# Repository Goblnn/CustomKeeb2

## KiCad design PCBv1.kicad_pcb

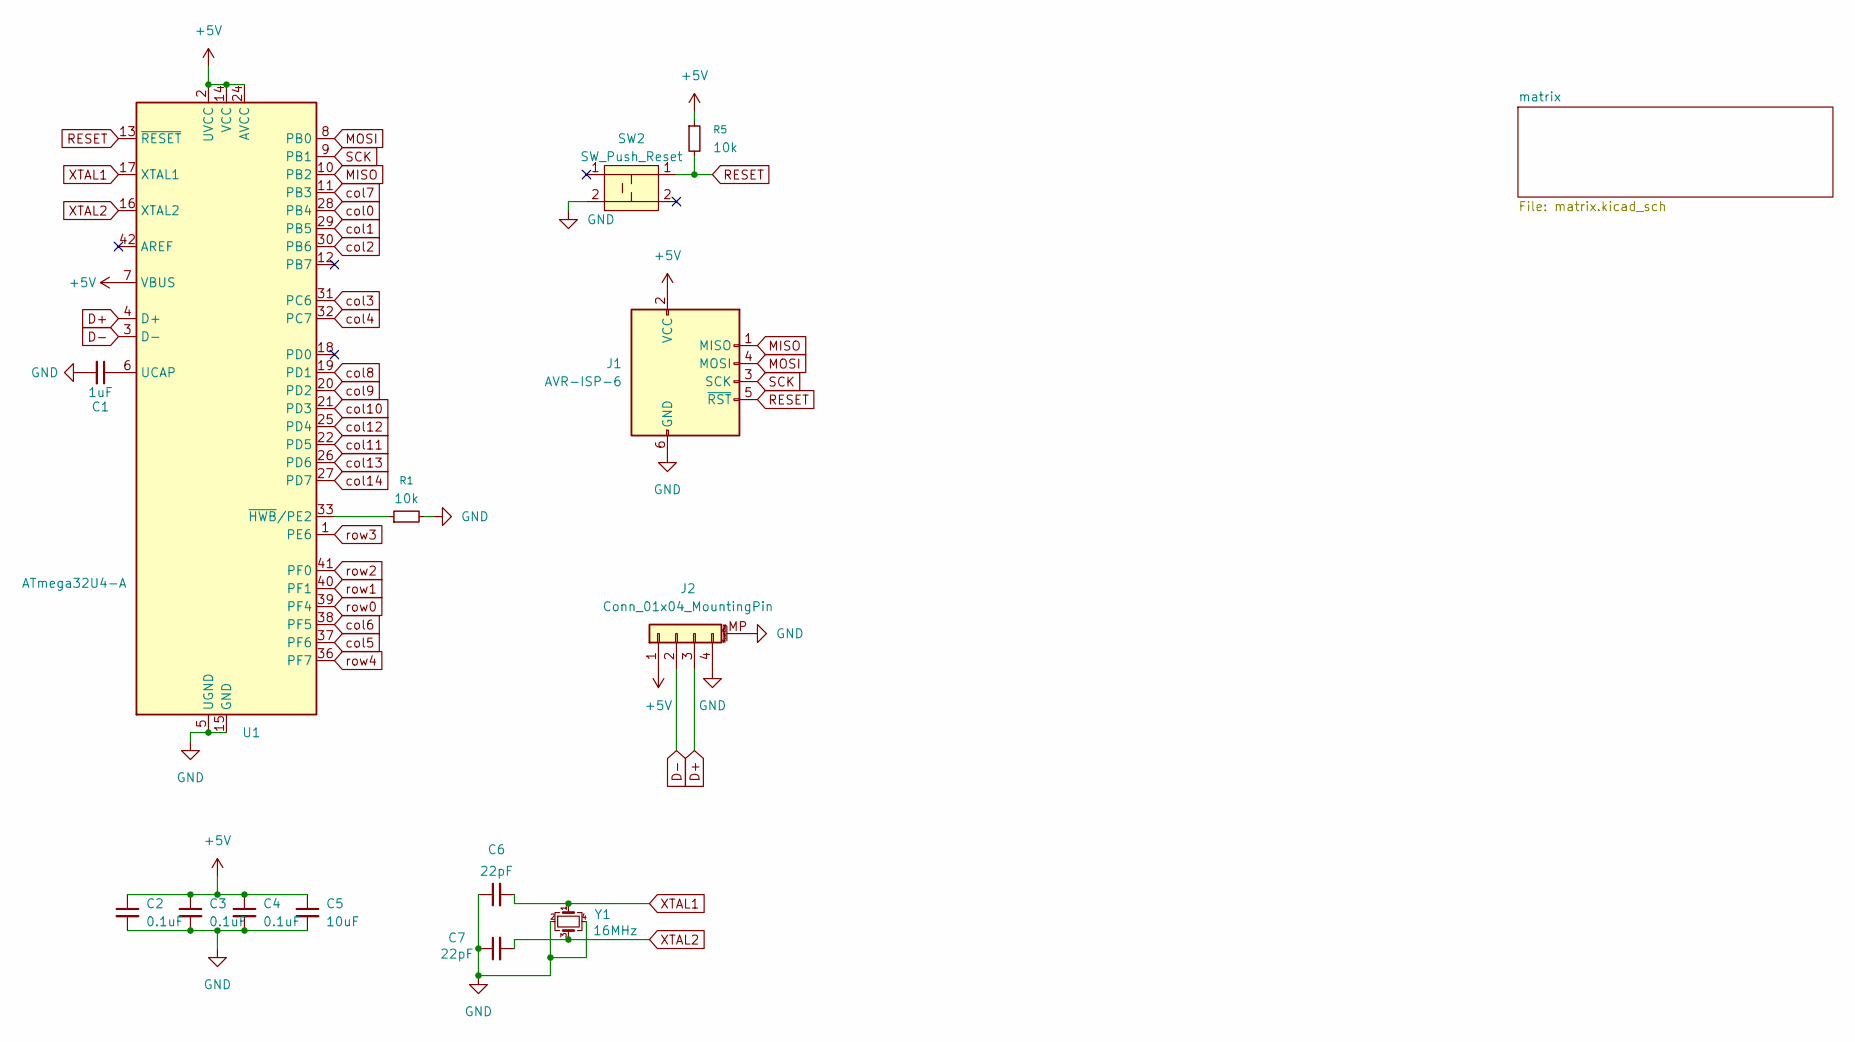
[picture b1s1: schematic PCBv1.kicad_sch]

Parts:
C1: 1uF; C_0805_2012Metric_Pad1.18x1.45mm_HandSolder
C2, C3, C4: 0.1uF; C_0805_2012Metric_Pad1.18x1.45mm_HandSolder
C5: 10uF; C_0805_2012Metric_Pad1.18x1.45mm_HandSolder
C6, C7: 22pF; C_0805_2012Metric_Pad1.18x1.45mm_HandSolder
J1: AVR-ISP-6; Reset_Pretty-Mask
J2: Conn_01x04_MountingPin; JST_SH_SM04B-SRSS-TB_1x04-1MP_P1.00mm_Horizontal
R1, R5: 10k; R_0805_2012Metric_Pad1.20x1.40mm_HandSolder
SW2: SW_Push_Reset; SW_SPST_SKQG_WithStem
U1: ATmega32U4-A; TQFP-44_10x10mm_P0.8mm
Y1: 16MHz; Crystal_SMD_3225-4Pin_3.2x2.5mm_HandSoldering

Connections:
+5V: C2.1, C3.1, C4.1, C5.1, J1.2 (VCC), J2.1, R5.1, U1.2 (UVCC), U1.7 (VBUS), U1.14 (VCC), U1.24 (AVCC), U1.34 (VCC), U1.44 (AVCC)
D+: J2.3, U1.4 (D+)
D-: J2.2, U1.3 (D-)
GND: C1.2, C2.2, C3.2, C4.2, C5.2, C6.1, C7.1, J1.6 (GND), J2.4, J2.MP (MountPin), R1.2, SW2.2, U1.5 (UGND), U1.15 (GND), U1.23 (GND), U1.35 (GND), U1.43 (GND), Y1.2, Y1.4
MISO: J1.1 (MISO), U1.10 (PB2)
MOSI: J1.4 (MOSI), U1.8 (PB0)
unnamed: C1.1, U1.6 (UCAP)
unnamed: R1.1, U1.33 (~HWB/PE2)
RESET: J1.5 (~RST), R5.2, SW2.1, U1.13 (~RESET)
SCK: J1.3 (SCK), U1.9 (PB1)
XTAL1: C6.2, U1.17 (XTAL1), Y1.1
XTAL2: C7.2, U1.16 (XTAL2), Y1.3
col0: U1.28 (PB4); also elsewhere on the board
col1: U1.29 (PB5); also elsewhere on the board
col2: U1.30 (PB6); also elsewhere on the board
col3: U1.31 (PC6); also elsewhere on the board
col4: U1.32 (PC7); also elsewhere on the board
col5: U1.37 (PF6); also elsewhere on the board
col6: U1.38 (PF5); also elsewhere on the board
col7: U1.11 (PB3); also elsewhere on the board
col8: U1.19 (PD1); also elsewhere on the board
col9: U1.20 (PD2); also elsewhere on the board
col10: U1.21 (PD3); also elsewhere on the board
col11: U1.22 (PD5); also elsewhere on the board
col12: U1.25 (PD4); also elsewhere on the board
col13: U1.26 (PD6); also elsewhere on the board
col14: U1.27 (PD7); also elsewhere on the board
row0: U1.39 (PF4); also elsewhere on the board
row1: U1.40 (PF1); also elsewhere on the board
row2: U1.41 (PF0); also elsewhere on the board
row3: U1.1 (PE6); also elsewhere on the board
row4: U1.36 (PF7); also elsewhere on the board

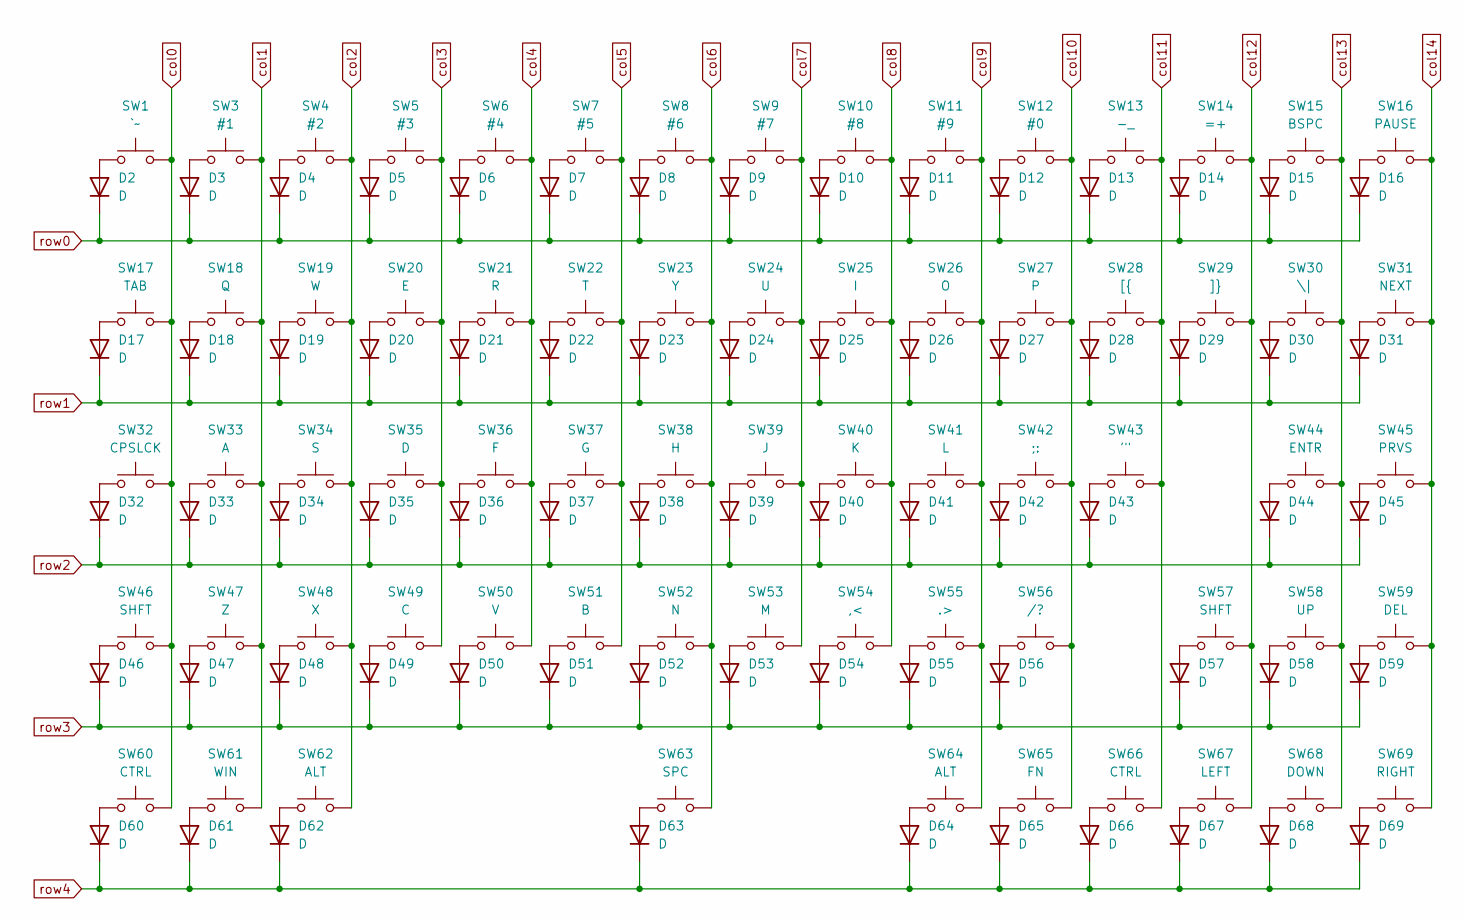
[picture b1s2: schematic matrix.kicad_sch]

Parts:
D2, D3, D4, D5, D6, D7, D8, D9, D10, D11, D12, D13, D14, D15, D16, D17, D18, D19, D20, D21, D22, D23, D24, D25, D26, D27, D28, D29, D30, D31, D32, D33, D34, D35, D36, D37, D38, D39, D40, D41, D42, D43, D44, D45, D46, D47, D48, D49, D50, D51, D52, D53, D54, D55, D56, D57, D58, D59, D60, D61, D62, D63, D64, D65, D66, D67, D68, D69: D; D_SOD-123
SW1: `~; MXOnly-1U-NoLED
SW3: #1; MXOnly-1U-NoLED
SW4: #2; MXOnly-1U-NoLED
SW5: #3; MXOnly-1U-NoLED
SW6: #4; MXOnly-1U-NoLED
SW7: #5; MXOnly-1U-NoLED
SW8: #6; MXOnly-1U-NoLED
SW9: #7; MXOnly-1U-NoLED
SW10: #8; MXOnly-1U-NoLED
SW11: #9; MXOnly-1U-NoLED
SW12: #0; MXOnly-1U-NoLED
SW13: -_; MXOnly-1U-NoLED
SW14: =+; MXOnly-1U-NoLED
SW15: BSPC; MXOnly-2U-NoLED
SW16: PAUSE; MXOnly-1U-NoLED
SW17: TAB; MXOnly-1.5U-NoLED
SW18: Q; MXOnly-1U-NoLED
SW19: W; MXOnly-1U-NoLED
SW20: E; MXOnly-1U-NoLED
SW21: R; MXOnly-1U-NoLED
SW22: T; MXOnly-1U-NoLED
SW23: Y; MXOnly-1U-NoLED
SW24: U; MXOnly-1U-NoLED
SW25: I; MXOnly-1U-NoLED
SW26: O; MXOnly-1U-NoLED
SW27: P; MXOnly-1U-NoLED
SW28: [{; MXOnly-1U-NoLED
SW29: ]}; MXOnly-1U-NoLED
SW30: \|; MXOnly-1.5U-NoLED
SW31: NEXT; MXOnly-1U-NoLED
SW32: CPSLCK; MXOnly-1.75U-NoLED
SW33: A; MXOnly-1U-NoLED
SW34: S; MXOnly-1U-NoLED
SW35: D; MXOnly-1U-NoLED
SW36: F; MXOnly-1U-NoLED
SW37: G; MXOnly-1U-NoLED
SW38: H; MXOnly-1U-NoLED
SW39: J; MXOnly-1U-NoLED
SW40: K; MXOnly-1U-NoLED
SW41: L; MXOnly-1U-NoLED
SW42: ;:; MXOnly-1U-NoLED
SW43: '"; MXOnly-1U-NoLED
SW44: ENTR; MXOnly-2.25U-NoLED
SW45: PRVS; MXOnly-1U-NoLED
SW46: SHFT; MXOnly-2.25U-NoLED
SW47: Z; MXOnly-1U-NoLED
SW48: X; MXOnly-1U-NoLED
SW49: C; MXOnly-1U-NoLED
SW50: V; MXOnly-1U-NoLED
SW51: B; MXOnly-1U-NoLED
SW52: N; MXOnly-1U-NoLED
SW53: M; MXOnly-1U-NoLED
SW54: ,<; MXOnly-1U-NoLED
SW55: .>; MXOnly-1U-NoLED
SW56: /?; MXOnly-1U-NoLED
SW57: SHFT; MXOnly-1.75U-NoLED
SW58: UP; MXOnly-1U-NoLED
SW59: DEL; MXOnly-1U-NoLED
SW60: CTRL; MXOnly-1.25U-NoLED
SW61: WIN; MXOnly-1.25U-NoLED
SW62: ALT; MXOnly-1.25U-NoLED
SW63: SPC; MXOnly-6.25U-NoLED
SW64: ALT; MXOnly-1U-NoLED
SW65: FN; MXOnly-1U-NoLED
SW66: CTRL; MXOnly-1U-NoLED
SW67: LEFT; MXOnly-1U-NoLED
SW68: DOWN; MXOnly-1U-NoLED
SW69: RIGHT; MXOnly-1U-NoLED

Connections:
unnamed: D2.2 (A), SW1.1
unnamed: D3.2 (A), SW3.1
unnamed: D4.2 (A), SW4.1
unnamed: D5.2 (A), SW5.1
unnamed: D6.2 (A), SW6.1
unnamed: D7.2 (A), SW7.1
unnamed: D8.2 (A), SW8.1
unnamed: D9.2 (A), SW9.1
unnamed: D10.2 (A), SW10.1
unnamed: D11.2 (A), SW11.1
unnamed: D12.2 (A), SW12.1
unnamed: D13.2 (A), SW13.1
unnamed: D14.2 (A), SW14.1
unnamed: D15.2 (A), SW15.1
unnamed: D16.2 (A), SW16.1
unnamed: D17.2 (A), SW17.1
unnamed: D18.2 (A), SW18.1
unnamed: D19.2 (A), SW19.1
unnamed: D20.2 (A), SW20.1
unnamed: D21.2 (A), SW21.1
unnamed: D22.2 (A), SW22.1
unnamed: D23.2 (A), SW23.1
unnamed: D24.2 (A), SW24.1
unnamed: D25.2 (A), SW25.1
unnamed: D26.2 (A), SW26.1
unnamed: D27.2 (A), SW27.1
unnamed: D28.2 (A), SW28.1
unnamed: D29.2 (A), SW29.1
unnamed: D30.2 (A), SW30.1
unnamed: D31.2 (A), SW31.1
unnamed: D32.2 (A), SW32.1
unnamed: D33.2 (A), SW33.1
unnamed: D34.2 (A), SW34.1
unnamed: D35.2 (A), SW35.1
unnamed: D36.2 (A), SW36.1
unnamed: D37.2 (A), SW37.1
unnamed: D38.2 (A), SW38.1
unnamed: D39.2 (A), SW39.1
unnamed: D40.2 (A), SW40.1
unnamed: D41.2 (A), SW41.1
unnamed: D42.2 (A), SW42.1
unnamed: D43.2 (A), SW43.1
unnamed: D44.2 (A), SW44.1
unnamed: D45.2 (A), SW45.1
unnamed: D46.2 (A), SW46.1
unnamed: D47.2 (A), SW47.1
unnamed: D48.2 (A), SW48.1
unnamed: D49.2 (A), SW49.1
unnamed: D50.2 (A), SW50.1
unnamed: D51.2 (A), SW51.1
unnamed: D52.2 (A), SW52.1
unnamed: D53.2 (A), SW53.1
unnamed: D54.2 (A), SW54.1
unnamed: D55.2 (A), SW55.1
unnamed: D56.2 (A), SW56.1
unnamed: D57.2 (A), SW57.1
unnamed: D58.2 (A), SW58.1
unnamed: D59.2 (A), SW59.1
unnamed: D60.2 (A), SW60.1
unnamed: D61.2 (A), SW61.1
unnamed: D62.2 (A), SW62.1
unnamed: D63.2 (A), SW63.1
unnamed: D64.2 (A), SW64.1
unnamed: D65.2 (A), SW65.1
unnamed: D66.2 (A), SW66.1
unnamed: D67.2 (A), SW67.1
unnamed: D68.2 (A), SW68.1
unnamed: D69.2 (A), SW69.1
col0: SW1.2, SW17.2, SW32.2, SW46.2, SW60.2; also elsewhere on the board
col1: SW3.2, SW18.2, SW33.2, SW47.2, SW61.2; also elsewhere on the board
col2: SW4.2, SW19.2, SW34.2, SW48.2, SW62.2; also elsewhere on the board
col3: SW5.2, SW20.2, SW35.2, SW49.2; also elsewhere on the board
col4: SW6.2, SW21.2, SW36.2, SW50.2; also elsewhere on the board
col5: SW7.2, SW22.2, SW37.2, SW51.2; also elsewhere on the board
col6: SW8.2, SW23.2, SW38.2, SW52.2, SW63.2; also elsewhere on the board
col7: SW9.2, SW24.2, SW39.2, SW53.2; also elsewhere on the board
col8: SW10.2, SW25.2, SW40.2, SW54.2; also elsewhere on the board
col9: SW11.2, SW26.2, SW41.2, SW55.2, SW64.2; also elsewhere on the board
col10: SW12.2, SW27.2, SW42.2, SW56.2, SW65.2; also elsewhere on the board
col11: SW13.2, SW28.2, SW43.2, SW66.2; also elsewhere on the board
col12: SW14.2, SW29.2, SW57.2, SW67.2; also elsewhere on the board
col13: SW15.2, SW30.2, SW44.2, SW58.2, SW68.2; also elsewhere on the board
col14: SW16.2, SW31.2, SW45.2, SW59.2, SW69.2; also elsewhere on the board
row0: D2.1 (K), D3.1 (K), D4.1 (K), D5.1 (K), D6.1 (K), D7.1 (K), D8.1 (K), D9.1 (K), D10.1 (K), D11.1 (K), D12.1 (K), D13.1 (K), D14.1 (K), D15.1 (K), D16.1 (K); also elsewhere on the board
row1: D17.1 (K), D18.1 (K), D19.1 (K), D20.1 (K), D21.1 (K), D22.1 (K), D23.1 (K), D24.1 (K), D25.1 (K), D26.1 (K), D27.1 (K), D28.1 (K), D29.1 (K), D30.1 (K), D31.1 (K); also elsewhere on the board
row2: D32.1 (K), D33.1 (K), D34.1 (K), D35.1 (K), D36.1 (K), D37.1 (K), D38.1 (K), D39.1 (K), D40.1 (K), D41.1 (K), D42.1 (K), D43.1 (K), D44.1 (K), D45.1 (K); also elsewhere on the board
row3: D46.1 (K), D47.1 (K), D48.1 (K), D49.1 (K), D50.1 (K), D51.1 (K), D52.1 (K), D53.1 (K), D54.1 (K), D55.1 (K), D56.1 (K), D57.1 (K), D58.1 (K), D59.1 (K); also elsewhere on the board
row4: D60.1 (K), D61.1 (K), D62.1 (K), D63.1 (K), D64.1 (K), D65.1 (K), D66.1 (K), D67.1 (K), D68.1 (K), D69.1 (K); also elsewhere on the board

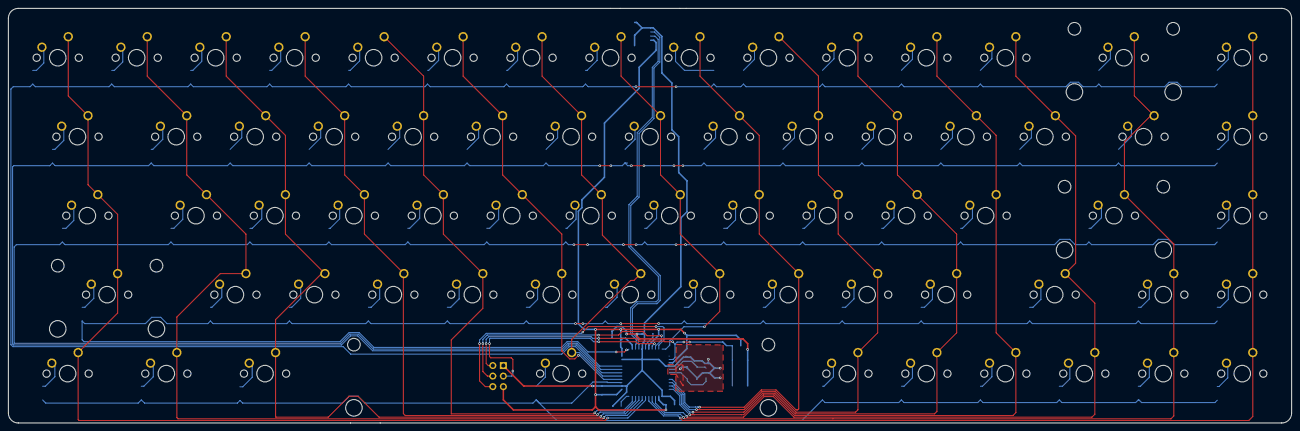
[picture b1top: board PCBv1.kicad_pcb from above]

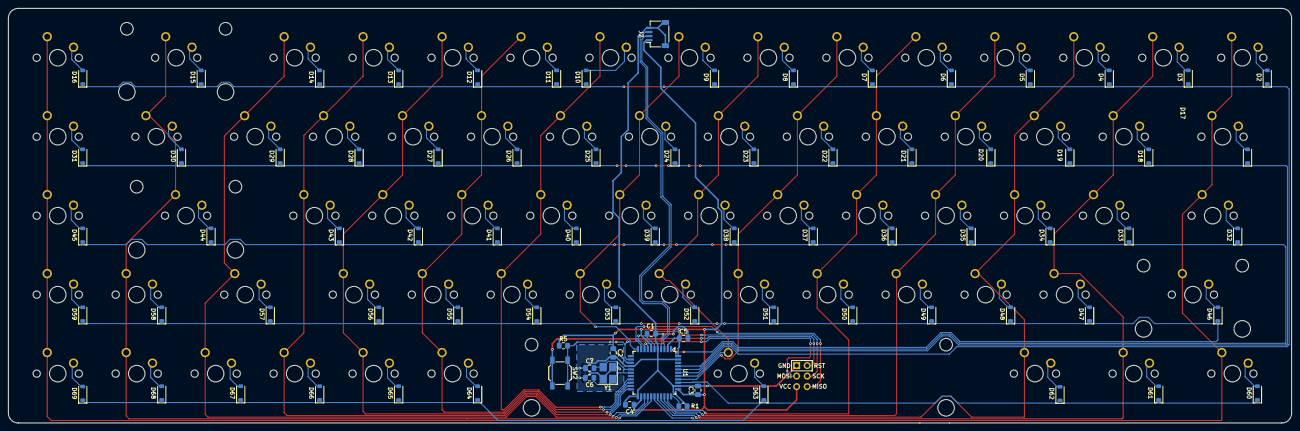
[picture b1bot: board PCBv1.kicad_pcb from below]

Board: 2 copper layers, 309.6 x 100.0 mm, 150 parts (82 on the bottom side), 100 nets.

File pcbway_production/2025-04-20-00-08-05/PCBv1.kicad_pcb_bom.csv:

Designator,Quantity,Value,Footprint,Package,MPN,DNP,Mount_Type,Description,Sim.Device,Sim.Pins
C1,1,1uF,C_0805_2012Metric_Pad1.18x1.45mm_HandSolder,,,,smt,"Unpolarized capacitor, small symbol",,
"C2, C3, C4",3,0.1uF,C_0805_2012Metric_Pad1.18x1.45mm_HandSolder,,,,smt,"Unpolarized capacitor, small symbol",,
C5,1,10uF,C_0805_2012Metric_Pad1.18x1.45mm_HandSolder,,,,smt,"Unpolarized capacitor, small symbol",,
"C6, C7",2,22pF,C_0805_2012Metric_Pad1.18x1.45mm_HandSolder,,,,smt,"Unpolarized capacitor, small symbol",,
D1,1,PRTR5V0U2X,SOT-143,,,,smt,"Ultra low capacitance double rail-to-rail ESD protection diode, SOT-143",,
"D10, D11, D12, D13, D14, D15, D16, D17, D18, D19, D2, D20, D21, D22, D23, D24, D25, D26, D27, D28, D29, D3, D30, D31, D32, D33, D34, D35, D36, D37, D38, D39, D4, D40, D41, D42, D43, D44, D45, D46, D47, D48, D49, D5, D50, D51, D52, D53, D54, D55, D56, D57, D58, D59, D6, D60, D61, D62, D63, D64, D65, D66, D67, D68, D69, D7, D8, D9",68,D,D_SOD-123,,,,smt,Diode,D,1=K 2=A
F1,1,500m,Fuse_1206_3216Metric_Pad1.42x1.75mm_HandSolder,,,,smt,"Resettable fuse, polymeric positive temperature coefficient, small symbol",,
J1,1,AVR-ISP-6,Reset_Pretty-Mask,,,,tht,Atmel 6-pin ISP connector,,
"R1, R5",2,10k,R_0805_2012Metric_Pad1.20x1.40mm_HandSolder,,,,smt,"Resistor, small symbol",,
"R6, R7",2,22,R_0805_2012Metric_Pad1.20x1.40mm_HandSolder,,,,smt,"Resistor, small symbol",,
"R8, R9",2,5.1k,R_0805_2012Metric_Pad1.20x1.40mm_HandSolder,,,,smt,"Resistor, small symbol",,
SW1,1,`~,MXOnly-1U-NoLED,,,,tht,"Push button switch, generic, two pins",,
SW10,1,#8,MXOnly-1U-NoLED,,,,tht,"Push button switch, generic, two pins",,
SW11,1,#9,MXOnly-1U-NoLED,,,,tht,"Push button switch, generic, two pins",,
SW12,1,#0,MXOnly-1U-NoLED,,,,tht,"Push button switch, generic, two pins",,
SW13,1,-_,MXOnly-1U-NoLED,,,,tht,"Push button switch, generic, two pins",,
SW14,1,=+,MXOnly-1U-NoLED,,,,tht,"Push button switch, generic, two pins",,
SW15,1,BSPC,MXOnly-2U-NoLED,,,,tht,"Push button switch, generic, two pins",,
SW16,1,PAUSE,MXOnly-1U-NoLED,,,,tht,"Push button switch, generic, two pins",,
SW17,1,TAB,MXOnly-1.5U-NoLED,,,,tht,"Push button switch, generic, two pins",,
SW18,1,Q,MXOnly-1U-NoLED,,,,tht,"Push button switch, generic, two pins",,
SW19,1,W,MXOnly-1U-NoLED,,,,tht,"Push button switch, generic, two pins",,
SW2,1,SW_Push_Reset,SW_SPST_SKQG_WithStem,,,,smt,,,
SW20,1,E,MXOnly-1U-NoLED,,,,tht,"Push button switch, generic, two pins",,
SW21,1,R,MXOnly-1U-NoLED,,,,tht,"Push button switch, generic, two pins",,
SW22,1,T,MXOnly-1U-NoLED,,,,tht,"Push button switch, generic, two pins",,
SW23,1,Y,MXOnly-1U-NoLED,,,,tht,"Push button switch, generic, two pins",,
SW24,1,U,MXOnly-1U-NoLED,,,,tht,"Push button switch, generic, two pins",,
SW25,1,I,MXOnly-1U-NoLED,,,,tht,"Push button switch, generic, two pins",,
SW26,1,O,MXOnly-1U-NoLED,,,,tht,"Push button switch, generic, two pins",,
SW27,1,P,MXOnly-1U-NoLED,,,,tht,"Push button switch, generic, two pins",,
SW28,1,[{,MXOnly-1U-NoLED,,,,tht,"Push button switch, generic, two pins",,
SW29,1,]},MXOnly-1U-NoLED,,,,tht,"Push button switch, generic, two pins",,
SW3,1,#1,MXOnly-1U-NoLED,,,,tht,"Push button switch, generic, two pins",,
SW30,1,\|,MXOnly-1.5U-NoLED,,,,tht,"Push button switch, generic, two pins",,
SW31,1,NEXT,MXOnly-1U-NoLED,,,,tht,"Push button switch, generic, two pins",,
SW32,1,CPSLCK,MXOnly-1.75U-NoLED,,,,tht,"Push button switch, generic, two pins",,
SW33,1,A,MXOnly-1U-NoLED,,,,tht,"Push button switch, generic, two pins",,
SW34,1,S,MXOnly-1U-NoLED,,,,tht,"Push button switch, generic, two pins",,
SW35,1,D,MXOnly-1U-NoLED,,,,tht,"Push button switch, generic, two pins",,
SW36,1,F,MXOnly-1U-NoLED,,,,tht,"Push button switch, generic, two pins",,
SW37,1,G,MXOnly-1U-NoLED,,,,tht,"Push button switch, generic, two pins",,
SW38,1,H,MXOnly-1U-NoLED,,,,tht,"Push button switch, generic, two pins",,
SW39,1,J,MXOnly-1U-NoLED,,,,tht,"Push button switch, generic, two pins",,
SW4,1,#2,MXOnly-1U-NoLED,,,,tht,"Push button switch, generic, two pins",,
SW40,1,K,MXOnly-1U-NoLED,,,,tht,"Push button switch, generic, two pins",,
SW41,1,L,MXOnly-1U-NoLED,,,,tht,"Push button switch, generic, two pins",,
SW42,1,;:,MXOnly-1U-NoLED,,,,tht,"Push button switch, generic, two pins",,
SW43,1,"'""",MXOnly-1U-NoLED,,,,tht,"Push button switch, generic, two pins",,
SW44,1,ENTR,MXOnly-2.25U-NoLED,,,,tht,"Push button switch, generic, two pins",,
SW45,1,PRVS,MXOnly-1U-NoLED,,,,tht,"Push button switch, generic, two pins",,
SW46,1,SHFT,MXOnly-2.25U-NoLED,,,,tht,"Push button switch, generic, two pins",,
SW47,1,Z,MXOnly-1U-NoLED,,,,tht,"Push button switch, generic, two pins",,
SW48,1,X,MXOnly-1U-NoLED,,,,tht,"Push button switch, generic, two pins",,
SW49,1,C,MXOnly-1U-NoLED,,,,tht,"Push button switch, generic, two pins",,
SW5,1,#3,MXOnly-1U-NoLED,,,,tht,"Push button switch, generic, two pins",,
SW50,1,V,MXOnly-1U-NoLED,,,,tht,"Push button switch, generic, two pins",,
SW51,1,B,MXOnly-1U-NoLED,,,,tht,"Push button switch, generic, two pins",,
SW52,1,N,MXOnly-1U-NoLED,,,,tht,"Push button switch, generic, two pins",,
SW53,1,M,MXOnly-1U-NoLED,,,,tht,"Push button switch, generic, two pins",,
SW54,1,",<",MXOnly-1U-NoLED,,,,tht,"Push button switch, generic, two pins",,
SW55,1,.>,MXOnly-1U-NoLED,,,,tht,"Push button switch, generic, two pins",,
SW56,1,/?,MXOnly-1U-NoLED,,,,tht,"Push button switch, generic, two pins",,
SW57,1,SHFT,MXOnly-1.75U-NoLED,,,,tht,"Push button switch, generic, two pins",,
SW58,1,UP,MXOnly-1U-NoLED,,,,tht,"Push button switch, generic, two pins",,
SW59,1,DEL,MXOnly-1U-NoLED,,,,tht,"Push button switch, generic, two pins",,
SW6,1,#4,MXOnly-1U-NoLED,,,,tht,"Push button switch, generic, two pins",,
SW60,1,CTRL,MXOnly-1.25U-NoLED,,,,tht,"Push button switch, generic, two pins",,
SW61,1,WIN,MXOnly-1.25U-NoLED,,,,tht,"Push button switch, generic, two pins",,
SW62,1,ALT,MXOnly-1.25U-NoLED,,,,tht,"Push button switch, generic, two pins",,
SW63,1,SPC,MXOnly-6.25U-NoLED,,,,tht,"Push button switch, generic, two pins",,
SW64,1,ALT,MXOnly-1U-NoLED,,,,tht,"Push button switch, generic, two pins",,
SW65,1,FN,MXOnly-1U-NoLED,,,,tht,"Push button switch, generic, two pins",,
SW66,1,CTRL,MXOnly-1U-NoLED,,,,tht,"Push button switch, generic, two pins",,
SW67,1,LEFT,MXOnly-1U-NoLED,,,,tht,"Push button switch, generic, two pins",,
SW68,1,DOWN,MXOnly-1U-NoLED,,,,tht,"Push button switch, generic, two pins",,
SW69,1,RIGHT,MXOnly-1U-NoLED,,,,tht,"Push button switch, generic, two pins",,
SW7,1,#5,MXOnly-1U-NoLED,,,,tht,"Push button switch, generic, two pins",,
SW8,1,#6,MXOnly-1U-NoLED,,,,tht,"Push button switch, generic, two pins",,
SW9,1,#7,MXOnly-1U-NoLED,,,,tht,"Push button switch, generic, two pins",,
U1,1,ATmega32U4-A,TQFP-44_10x10mm_P0.8mm,,,,smt,"16MHz, 32kB Flash, 2.5kB SRAM, 1kB EEPROM, USB 2.0, TQFP-44",,
USB1,1,HRO-TYPE-C-31-M-12,HRO-TYPE-C-31-M-12-HandSoldering,,,,smt,,,
Y1,1,16MHz,Crystal_SMD_3225-4Pin_3.2x2.5mm_HandSoldering,,,,smt,"Four pin crystal, GND on pins 2 and 4, small symbol",,

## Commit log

2025-04-21 stuff
2025-04-21 adas
2025-04-21 locked in
2025-04-21 done
2025-04-21 love updates on kicad close
2025-04-21 idek
2025-04-23 putting on new computer
2025-04-24 sdadad
2025-05-05 firmware start
2025-06-28 fix row3 pin
2025-06-29 update things
2025-10-07 smthn
2026-04-07 mnajksda
